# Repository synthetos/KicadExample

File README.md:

# LoadCellAmplifier
Tiny board for connecting Wheatstone bridge load cells to 3.3v ADC inputs

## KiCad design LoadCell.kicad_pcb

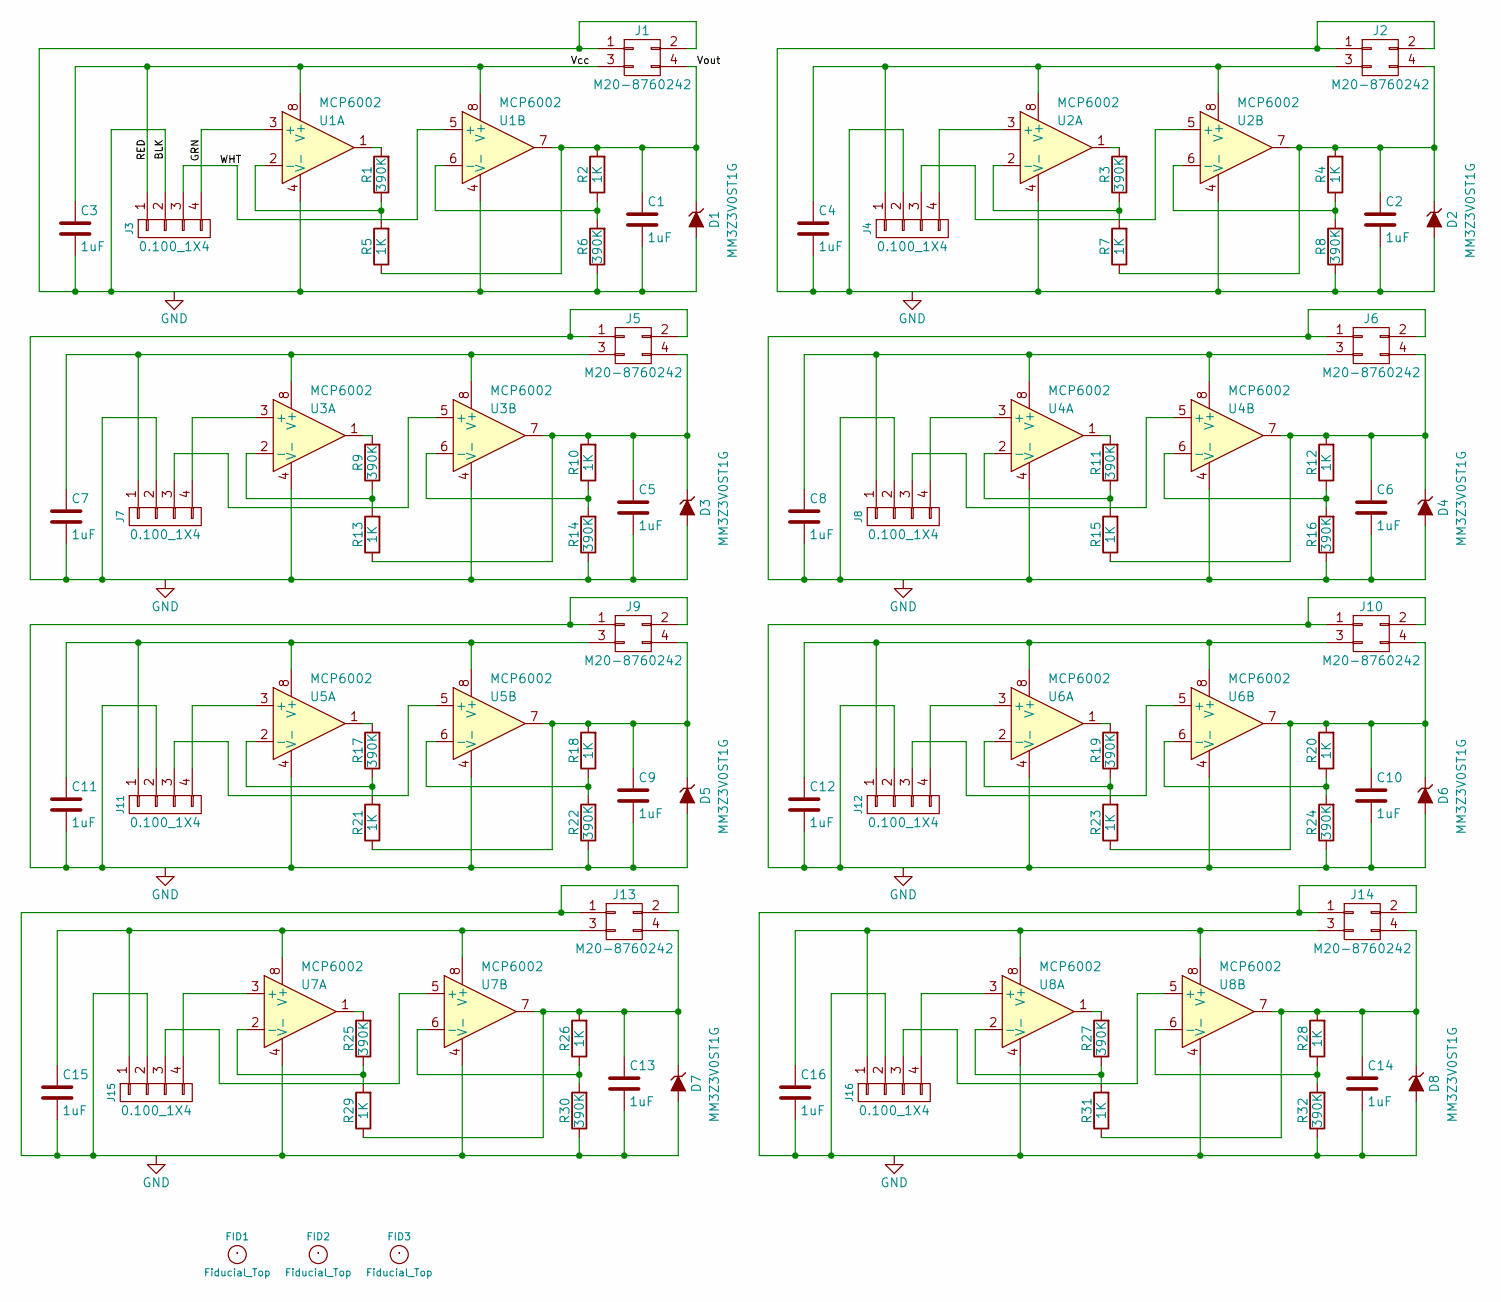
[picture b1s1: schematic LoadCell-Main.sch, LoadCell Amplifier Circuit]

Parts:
C1, C2, C3, C4, C5, C6, C7, C8, C9, C10, C11, C12, C13, C14, C15, C16: 1uF; C_0603
D1, D2, D3, D4, D5, D6, D7, D8: MM3Z3V0ST1G; SOD-323
FID1, FID2, FID3: Fiducial_Top; Fiducial_0.040_Top
J1, J2, J5, J6, J9, J10, J13, J14: M20-8760242; Pin_Header_Straight_2x02_Pitch2.54mm_SMD
J3, J4, J7, J8, J11, J12, J15, J16: 0.100_1X4; 0.100_1x4_micro
R1, R3, R6, R8, R9, R11, R14, R16, R17, R19, R22, R24, R25, R27, R30, R32: 390K; R_0603
R2, R4, R5, R7, R10, R12, R13, R15, R18, R20, R21, R23, R26, R28, R29, R31: 1K; R_0603
U1, U2, U3, U4, U5, U6, U7, U8: MCP6002; TSSOP-8_4.4x3mm_Pitch0.65mm

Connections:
/Main Sheet/GRN: J3.4, U1.3 (+)
/Main Sheet/RED: C3.1, J1.3, J3.1, U1.8 (V+)
/Main Sheet/Vout: C1.1, D1.1 (K), J1.4, R2.2, R5.1, U1.7
/Main Sheet/WHT: J3.3, U1.5 (+)
unnamed: C2.1, D2.1 (K), J2.4, R4.2, R7.1, U2.7
unnamed: C4.1, J2.3, J4.1, U2.8 (V+)
unnamed: C5.1, D3.1 (K), J5.4, R10.2, R13.1, U3.7
unnamed: C6.1, D4.1 (K), J6.4, R12.2, R15.1, U4.7
unnamed: C7.1, J5.3, J7.1, U3.8 (V+)
unnamed: C8.1, J6.3, J8.1, U4.8 (V+)
unnamed: C9.1, D5.1 (K), J9.4, R18.2, R21.1, U5.7
unnamed: C10.1, D6.1 (K), J10.4, R20.2, R23.1, U6.7
unnamed: C11.1, J9.3, J11.1, U5.8 (V+)
unnamed: C12.1, J10.3, J12.1, U6.8 (V+)
unnamed: C13.1, D7.1 (K), J13.4, R26.2, R29.1, U7.7
unnamed: C14.1, D8.1 (K), J14.4, R28.2, R31.1, U8.7
unnamed: C15.1, J13.3, J15.1, U7.8 (V+)
unnamed: C16.1, J14.3, J16.1, U8.8 (V+)
unnamed: J4.3, U2.5 (+)
unnamed: J4.4, U2.3 (+)
unnamed: J7.3, U3.5 (+)
unnamed: J7.4, U3.3 (+)
unnamed: J8.3, U4.5 (+)
unnamed: J8.4, U4.3 (+)
unnamed: J11.3, U5.5 (+)
unnamed: J11.4, U5.3 (+)
unnamed: J12.3, U6.5 (+)
unnamed: J12.4, U6.3 (+)
unnamed: J15.3, U7.5 (+)
unnamed: J15.4, U7.3 (+)
unnamed: J16.3, U8.5 (+)
unnamed: J16.4, U8.3 (+)
unnamed: R1.1, R5.2, U1.2 (-)
unnamed: R1.2, U1.1
unnamed: R2.1, R6.2, U1.6 (-)
unnamed: R3.1, R7.2, U2.2 (-)
unnamed: R3.2, U2.1
unnamed: R4.1, R8.2, U2.6 (-)
unnamed: R9.2, U3.1
unnamed: R10.1, R14.2, U3.6 (-)
unnamed: R11.1, R15.2, U4.2 (-)
unnamed: R11.2, U4.1
unnamed: R12.1, R16.2, U4.6 (-)
unnamed: R9.1, R13.2, U3.2 (-)
unnamed: R17.1, R21.2, U5.2 (-)
unnamed: R17.2, U5.1
unnamed: R18.1, R22.2, U5.6 (-)
unnamed: R19.1, R23.2, U6.2 (-)
unnamed: R19.2, U6.1
unnamed: R20.1, R24.2, U6.6 (-)
unnamed: R25.1, R29.2, U7.2 (-)
unnamed: R25.2, U7.1
unnamed: R26.1, R30.2, U7.6 (-)
unnamed: R27.1, R31.2, U8.2 (-)
unnamed: R27.2, U8.1
unnamed: R28.1, R32.2, U8.6 (-)

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
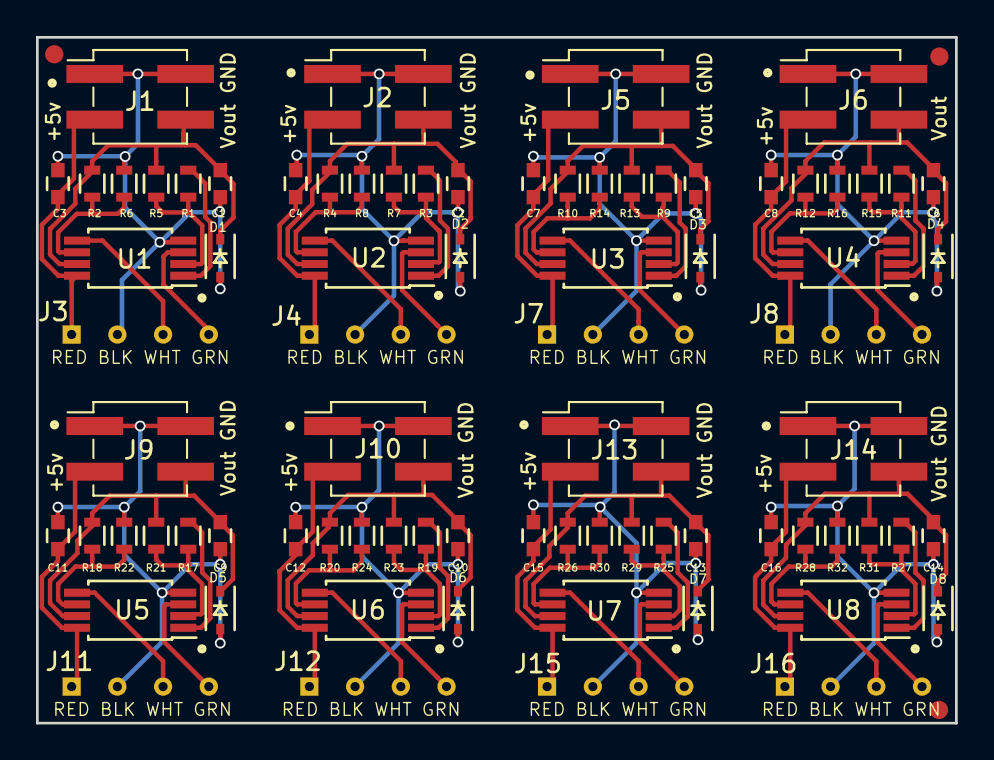
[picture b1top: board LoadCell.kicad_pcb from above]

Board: 2 copper layers, 51.1 x 38.1 mm, 83 parts (0 on the bottom side), 64 nets.

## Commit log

2018-02-12 First commit with some actual content
2018-02-12 Single circuit placed
2018-02-12 Changed gitignore
2018-02-15 Revised circuit. Schematic revised, layout not yet.
2018-02-15 First unit layout
2018-02-16 Changed load cell termination pads
2018-02-20 Added fiducials, final check
2018-02-22 Submitted to OSHpark
2018-04-22 Started changes the version 2
2018-04-22 Checkpoint
2018-04-23 Checkpoint - first unit laid out
2018-04-23 Parts placed
2018-04-23 Fully routed panel of 8 adapters
2018-04-24 Update before generating project outputs
2018-06-20 Latest commit
2018-07-03 Added GlobalLibrary directory
